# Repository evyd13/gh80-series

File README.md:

# GH80 series keyboard PCBs for Cherry boards

Please read the license before use. Each board has its own BOM and gerber files included.

These boards have been tested by numerous people, but I cannot guarantee that they work for your board.

I will not help you when you fuck up your soldering work, lol (though I might because I'm just too kind)

Oh by the way, use kicad nightly to open the source files.

## GH80-3000 vs GH80-3003
The 3000 is made by someone else, and the 3003 is mine. See it as my take on the same idea.

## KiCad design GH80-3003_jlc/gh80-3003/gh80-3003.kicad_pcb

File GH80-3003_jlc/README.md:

# GH80-3003 jlc

PCB designed by evyd13, edited to be assembled at jlcpcb by ebastler

Gerber, BOM and CPL file for jlcpcb assembly are included. They have been tested and confirmed working, but I can not guarantee that jlcpcb will not make any breaking changes. jlcpcb stocks might change, parts could go EOL. Compare MCU/diode/SRV05 rotation before ordering, to be sure.

If you order a small batch and sell the unneeded ones, please keep the license in mind.

## jlcpcb components (already in BOM/assembly files)

| Reference  | jlcpcb part # | Description    | Value    | Package  | Amount |
| ---------- | ------------- | -------------- | -------- | -------- | ------:|
| C1-C4      | C49678        | Capacitor      | 0.1 uF   | 0805     | 4      |
| C5         | C1779         | Capacitor      | 4.7 uF   | 0805     | 1      |
| C6         | C28323        | Capacitor      | 1 uF     | 0805     | 1      |
| C7, C8     | C1653         | Capacitor      | 22 pF    | 0603     | 2      |
| D1-D114    | C81598        | Diode          | 1N4148   | SOD-123  | 114    |
| F1         | C183290       | Fuse           | 750 mA   | 1206     | 1      |
| R1, R2     | C17561        | Resistor       | 22       | 0805     | 2      |
| R3, R4, R6 | C17513        | Resistor       | 1 k      | 0805     | 3      |
| R5, R6     | C17414        | Resistor       | 10 k     | 0805     | 2      |
| U1         | C44854        | MCU            | 32U4     | QFP-44   | 1      |
| U2         | C85364        | ESD Protection | SRV-05   | SOT-23-6 | 1      |
| Y1         | C13738        | Crystal        | 16 MHz   | 3225-4   | 1      |

## Other parts
| Reference  | LCSC part #   | Description   | Value    | Package  | Amount  |
| ---------- | ------------- | ------------- | -------- | -------- | -------:|
| K1-K114    |               | Keyswitch     |          | MX-like  | depends |
| L1-L3      |               | LED           |          | 3 mm THT | 3       |
| J2-J4      | C105424       | Connector     | mini USB | SMD      | 3       |
| SW1        | C92584        | Pushbutton    |          | SMD      | 1       |

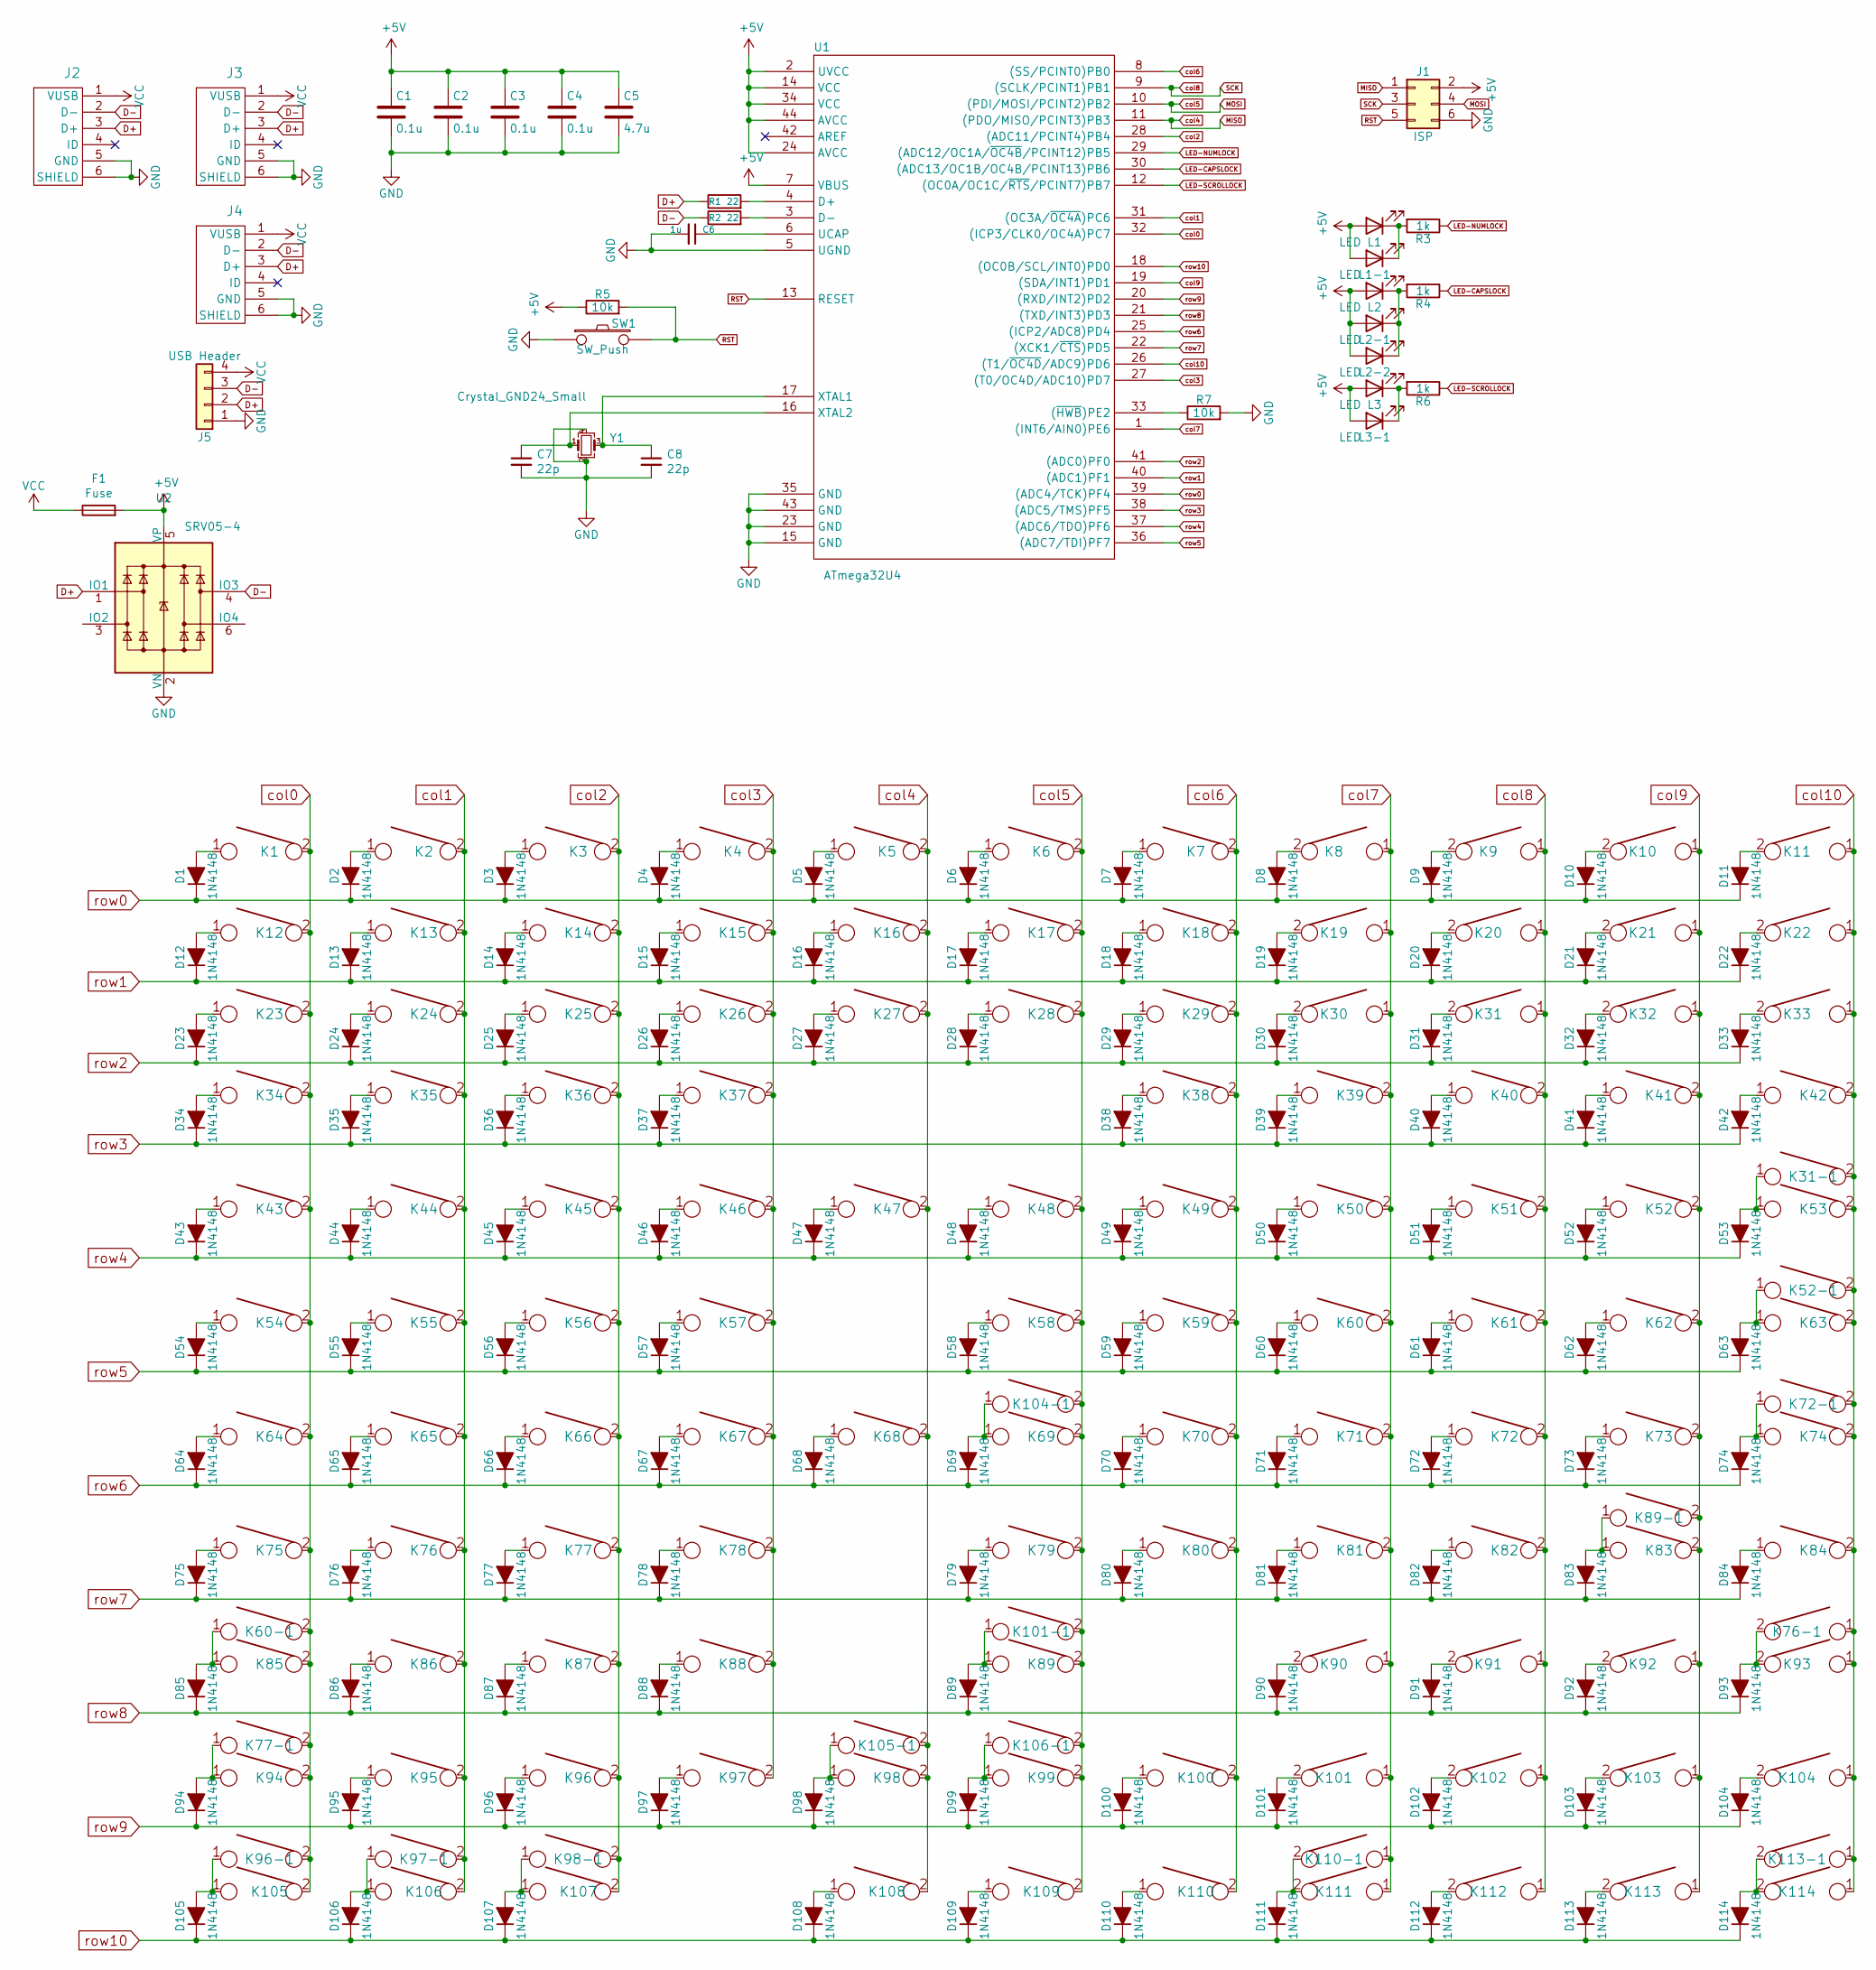
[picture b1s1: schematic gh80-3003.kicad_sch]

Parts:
C1, C2, C3, C4: 0.1u; C_0805_2012Metric; LCSC C49678
C5: 4.7u; C_0805_2012Metric; LCSC C1779
C6: 1u; C_0805_2012Metric; LCSC C28323
C7, C8: 22p; C_0603_1608Metric; LCSC C1653
D1, D2, D3, D4, D5, D6, D7, D8, D9, D10, D11, D12, D13, D14, D15, D16, D17, D18, D19, D20, D21, D22, D23, D24, D25, D26, D27, D28, D29, D30, D31, D32, D33, D34, D35, D36, D37, D38, D39, D40, D41, D42, D43, D44, D45, D46, D47, D48, D49, D50, D51, D52, D53, D54, D55, D56, D57, D58, D59, D60, D61, D62, D63, D64, D65, D66, D67, D68, D69, D70, D71, D72, D73, D74, D75, D76, D77, D78, D79, D80, D81, D82, D83, D84, D85, D86, D87, D88, D89, D90, D91, D92, D93, D94, D95, D96, D97, D98, D99, D100, D101, D102, D103, D104, D105, D106, D107, D108, D109, D110, D111, D112, D113, D114: 1N4148; D_SOD-123; LCSC C81598
F1: Fuse; Fuse_1206_3216Metric; LCSC C183290
J1: ISP; isp_standard
J2, J3, J4: USB_mini_micro_B; USB_Mini_SMD
J5: USB Header; USB_breakout
K1, K2, K3, K4, K5, K6, K7, K8, K9, K10, K11, K12, K13, K14, K15, K16, K17, K18, K19, K20, K21, K22, K24, K25, K26, K27, K28, K29, K30, K31, K31-1, K32, K33, K34, K35, K36, K37, K38, K39, K40, K41, K42, K43, K44, K45, K46, K47, K48, K49, K50, K51, K52, K52-1, K54, K55, K56, K57, K58, K59, K60, K61, K62, K64, K65, K66, K67, K70, K71, K72, K73, K75, K76, K76-1, K77, K78, K79, K80, K81, K82, K84, K86, K87, K88, K90, K91, K92, K95, K96, K97, K98, K100, K101, K102, K103, K104, K106, K108, K109, K110, K110-1, K112, K113, K113-1: KEYSW; CHERRY_PLATE_100H
K23, K63, K69, K99, K105, K107: KEYSW; CHERRY_PLATE_150H
K53, K111: KEYSW; CHERRY_PCB_200H
K60-1, K68, K77-1, K96-1, K97-1, K98-1, K104-1, K105-1, K106-1: KEYSW; CHERRY_PLATE_125H
K72-1: KEYSW; CHERRY_PCB_200H_V
K74, K94: KEYSW; CHERRY_PCB_225H
K83: KEYSW; CHERRY_PCB_275H
K85, K89-1: KEYSW; CHERRY_PLATE_175H
K89: KEYSW; CHERRY_PCB_700H
K93, K114: KEYSW; CHERRY_PCB_200H_V_F
K101-1: KEYSW; CHERRY_PCB_625H
L1, L2, L3: LED; LED_D3.0mm
L1-1, L2-1, L2-2, L3-1: LED; CHERRY_MX_LED
R1, R2: 22; R_0805_2012Metric; LCSC C17561
R3, R4, R6: 1k; R_0805_2012Metric; LCSC C17513
R5, R7: 10k; R_0805_2012Metric; LCSC C17414
SW1: SW_Push; SW_SPST_TL3342
U1: ATmega32U4; TQFP-44_10x10mm_P0.8mm; LCSC C44854
U2: SRV05-4; SOT-23-6; LCSC C85364
Y1: Crystal_GND24_Small; Crystal_SMD_3225-4Pin_3.2x2.5mm; LCSC C13738

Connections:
+5V: C1.1, C2.1, C3.1, C4.1, C5.1, F1.2, J1.2, L1.2 (A), L1-1.2 (A), L2.2 (A), L2-1.2 (A), L2-2.2 (A), L3.2 (A), L3-1.2 (A), R5.1, U1.2 (UVCC), U1.7 (VBUS), U1.14 (VCC), U1.24 (AVCC), U1.34 (VCC), U1.44 (AVCC), U2.5 (VP)
D+: J2.3 (D+), J3.3 (D+), J4.3 (D+), J5.2, R1.1, U2.1 (IO1)
D-: J2.2 (D-), J3.2 (D-), J4.2 (D-), J5.3, R2.1, U2.4 (IO3)
GND: C1.2, C2.2, C3.2, C4.2, C5.2, C6.2, C7.2, C8.2, J1.6, J2.5 (GND), J2.6 (SHIELD), J3.5 (GND), J3.6 (SHIELD), J4.5 (GND), J4.6 (SHIELD), J5.1, R7.2, SW1.1, U1.5 (UGND), U1.15 (GND), U1.23 (GND), U1.35 (GND), U1.43 (GND), U2.2 (VN), Y1.2, Y1.4
LED-CAPSLOCK: R4.1, U1.30 ((ADC13/OC1B/OC4B/PCINT13)PB6)
LED-NUMLOCK: R3.1, U1.29 ((ADC12/OC1A/~OC4B~/PCINT12)PB5)
LED-SCROLLOCK: R6.1, U1.12 ((OC0A/OC1C/~RTS~/PCINT7)PB7)
MISO: J1.1, K5.2, K16.2, K27.2, K47.2, K68.2, K98.2, K105-1.2, K108.2, U1.11 ((PDO/MISO/PCINT3)PB3)
MOSI: J1.4, K6.2, K17.2, K28.2, K48.2, K58.2, K69.2, K79.2, K89.2, K99.2, K101-1.2, K104-1.2, K106-1.2, K109.2, U1.10 ((PDI/MOSI/PCINT2)PB2)
unnamed: C6.1, U1.6 (UCAP)
unnamed: C7.1, U1.16 (XTAL2), Y1.1
unnamed: C8.1, U1.17 (XTAL1), Y1.3
unnamed: D1.2 (A), K1.1
unnamed: D2.2 (A), K2.1
unnamed: D3.2 (A), K3.1
unnamed: D4.2 (A), K4.1
unnamed: D5.2 (A), K5.1
unnamed: D6.2 (A), K6.1
unnamed: D7.2 (A), K7.1
unnamed: D8.2 (A), K8.2
unnamed: D9.2 (A), K9.2
unnamed: D10.2 (A), K10.2
unnamed: D11.2 (A), K11.2
unnamed: D12.2 (A), K12.1
unnamed: D13.2 (A), K13.1
unnamed: D14.2 (A), K14.1
unnamed: D15.2 (A), K15.1
unnamed: D16.2 (A), K16.1
unnamed: D17.2 (A), K17.1
unnamed: D18.2 (A), K18.1
unnamed: D19.2 (A), K19.2
unnamed: D20.2 (A), K20.2
unnamed: D21.2 (A), K21.2
unnamed: D22.2 (A), K22.2
unnamed: D23.2 (A), K23.1
unnamed: D24.2 (A), K24.1
unnamed: D25.2 (A), K25.1
unnamed: D26.2 (A), K26.1
unnamed: D27.2 (A), K27.1
unnamed: D28.2 (A), K28.1
unnamed: D29.2 (A), K29.1
unnamed: D30.2 (A), K30.2
unnamed: D31.2 (A), K31.2
unnamed: D32.2 (A), K32.2
unnamed: D33.2 (A), K33.2
unnamed: D34.2 (A), K34.1
unnamed: D35.2 (A), K35.1
unnamed: D36.2 (A), K36.1
unnamed: D37.2 (A), K37.1
unnamed: D38.2 (A), K38.1
unnamed: D39.2 (A), K39.1
unnamed: D40.2 (A), K40.1
unnamed: D41.2 (A), K41.1
unnamed: D42.2 (A), K42.1
unnamed: D43.2 (A), K43.1
unnamed: D44.2 (A), K44.1
unnamed: D45.2 (A), K45.1
unnamed: D46.2 (A), K46.1
unnamed: D47.2 (A), K47.1
unnamed: D48.2 (A), K48.1
unnamed: D49.2 (A), K49.1
unnamed: D50.2 (A), K50.1
unnamed: D51.2 (A), K51.1
unnamed: D52.2 (A), K52.1
unnamed: D53.2 (A), K31-1.1, K53.1
unnamed: D54.2 (A), K54.1
unnamed: D55.2 (A), K55.1
unnamed: D56.2 (A), K56.1
unnamed: D57.2 (A), K57.1
unnamed: D58.2 (A), K58.1
unnamed: D59.2 (A), K59.1
unnamed: D60.2 (A), K60.1
unnamed: D61.2 (A), K61.1
unnamed: D62.2 (A), K62.1
unnamed: D63.2 (A), K52-1.1, K63.1
unnamed: D64.2 (A), K64.1
unnamed: D65.2 (A), K65.1
unnamed: D66.2 (A), K66.1
unnamed: D67.2 (A), K67.1
unnamed: D68.2 (A), K68.1
unnamed: D69.2 (A), K69.1, K104-1.1
unnamed: D70.2 (A), K70.1
unnamed: D71.2 (A), K71.1
unnamed: D72.2 (A), K72.1
unnamed: D73.2 (A), K73.1
unnamed: D74.2 (A), K72-1.1, K74.1
unnamed: D75.2 (A), K75.1
unnamed: D76.2 (A), K76.1
unnamed: D77.2 (A), K77.1
unnamed: D78.2 (A), K78.1
unnamed: D79.2 (A), K79.1
unnamed: D80.2 (A), K80.1
unnamed: D81.2 (A), K81.1
unnamed: D82.2 (A), K82.1
unnamed: D83.2 (A), K83.1, K89-1.1
unnamed: D84.2 (A), K84.1
unnamed: D85.2 (A), K60-1.1, K85.1
unnamed: D86.2 (A), K86.1
unnamed: D87.2 (A), K87.1
unnamed: D88.2 (A), K88.1
unnamed: D89.2 (A), K89.1, K101-1.1
unnamed: D90.2 (A), K90.2
unnamed: D91.2 (A), K91.2
unnamed: D92.2 (A), K92.2
unnamed: D93.2 (A), K76-1.2, K93.2
unnamed: D94.2 (A), K77-1.1, K94.1
unnamed: D95.2 (A), K95.1
unnamed: D96.2 (A), K96.1
unnamed: D97.2 (A), K97.1
unnamed: D98.2 (A), K98.1, K105-1.1
unnamed: D99.2 (A), K99.1, K106-1.1
unnamed: D100.2 (A), K100.1
unnamed: D101.2 (A), K101.2
unnamed: D102.2 (A), K102.2
unnamed: D103.2 (A), K103.2
unnamed: D104.2 (A), K104.2
unnamed: D105.2 (A), K96-1.1, K105.1
unnamed: D106.2 (A), K97-1.1, K106.1
unnamed: D107.2 (A), K98-1.1, K107.1
unnamed: D108.2 (A), K108.1
unnamed: D109.2 (A), K109.1
unnamed: D110.2 (A), K110.1
unnamed: D111.2 (A), K110-1.2, K111.2
unnamed: D112.2 (A), K112.2
unnamed: D113.2 (A), K113.2
unnamed: D114.2 (A), K113-1.2, K114.2
unnamed: L1.1 (K), L1-1.1 (K), R3.2
unnamed: L2.1 (K), L2-1.1 (K), L2-2.1 (K), R4.2
unnamed: L3.1 (K), L3-1.1 (K), R6.2
unnamed: R1.2, U1.4 (D+)
unnamed: R2.2, U1.3 (D-)
unnamed: R7.1, U1.33 ((~HWB~)PE2)
RST: J1.5, R5.2, SW1.2, U1.13 (RESET)
SCK: J1.3, K9.1, K20.1, K31.1, K40.2, K51.2, K61.2, K72.2, K82.2, K91.1, K102.1, K112.1, U1.9 ((SCLK/PCINT1)PB1)
VCC: F1.1, J2.1 (VUSB), J3.1 (VUSB), J4.1 (VUSB), J5.4
col0: K1.2, K12.2, K23.2, K34.2, K43.2, K54.2, K60-1.2, K64.2, K75.2, K77-1.2, K85.2, K94.2, K96-1.2, K105.2, U1.32 ((ICP3/CLK0/OC4A)PC7)
col1: K2.2, K13.2, K24.2, K35.2, K44.2, K55.2, K65.2, K76.2, K86.2, K95.2, K97-1.2, K106.2, U1.31 ((OC3A/~OC4A~)PC6)
col2: K3.2, K14.2, K25.2, K36.2, K45.2, K56.2, K66.2, K77.2, K87.2, K96.2, K98-1.2, K107.2, U1.28 ((ADC11/PCINT4)PB4)
col3: K4.2, K15.2, K26.2, K37.2, K46.2, K57.2, K67.2, K78.2, K88.2, K97.2, U1.27 ((T0/OC4D/ADC10)PD7)
col6: K7.2, K18.2, K29.2, K38.2, K49.2, K59.2, K70.2, K80.2, K100.2, K110.2, U1.8 ((SS/PCINT0)PB0)
col7: K8.1, K19.1, K30.1, K39.2, K50.2, K60.2, K71.2, K81.2, K90.1, K101.1, K110-1.1, K111.1, U1.1 ((INT6/AIN0)PE6)
col9: K10.1, K21.1, K32.1, K41.2, K52.2, K62.2, K73.2, K83.2, K89-1.2, K92.1, K103.1, K113.1, U1.19 ((SDA/INT1)PD1)
col10: K11.1, K22.1, K31-1.2, K33.1, K42.2, K52-1.2, K53.2, K63.2, K72-1.2, K74.2, K76-1.1, K84.2, K93.1, K104.1, K113-1.1, K114.1, U1.26 ((T1/~OC4D~/ADC9)PD6)
row0: D1.1 (K), D2.1 (K), D3.1 (K), D4.1 (K), D5.1 (K), D6.1 (K), D7.1 (K), D8.1 (K), D9.1 (K), D10.1 (K), D11.1 (K), U1.39 ((ADC4/TCK)PF4)
row1: D12.1 (K), D13.1 (K), D14.1 (K), D15.1 (K), D16.1 (K), D17.1 (K), D18.1 (K), D19.1 (K), D20.1 (K), D21.1 (K), D22.1 (K), U1.40 ((ADC1)PF1)
row2: D23.1 (K), D24.1 (K), D25.1 (K), D26.1 (K), D27.1 (K), D28.1 (K), D29.1 (K), D30.1 (K), D31.1 (K), D32.1 (K), D33.1 (K), U1.41 ((ADC0)PF0)
row3: D34.1 (K), D35.1 (K), D36.1 (K), D37.1 (K), D38.1 (K), D39.1 (K), D40.1 (K), D41.1 (K), D42.1 (K), U1.38 ((ADC5/TMS)PF5)
row4: D43.1 (K), D44.1 (K), D45.1 (K), D46.1 (K), D47.1 (K), D48.1 (K), D49.1 (K), D50.1 (K), D51.1 (K), D52.1 (K), D53.1 (K), U1.37 ((ADC6/TDO)PF6)
row5: D54.1 (K), D55.1 (K), D56.1 (K), D57.1 (K), D58.1 (K), D59.1 (K), D60.1 (K), D61.1 (K), D62.1 (K), D63.1 (K), U1.36 ((ADC7/TDI)PF7)
row6: D64.1 (K), D65.1 (K), D66.1 (K), D67.1 (K), D68.1 (K), D69.1 (K), D70.1 (K), D71.1 (K), D72.1 (K), D73.1 (K), D74.1 (K), U1.25 ((ICP2/ADC8)PD4)
row7: D75.1 (K), D76.1 (K), D77.1 (K), D78.1 (K), D79.1 (K), D80.1 (K), D81.1 (K), D82.1 (K), D83.1 (K), D84.1 (K), U1.22 ((XCK1/~CTS~)PD5)
row8: D85.1 (K), D86.1 (K), D87.1 (K), D88.1 (K), D89.1 (K), D90.1 (K), D91.1 (K), D92.1 (K), D93.1 (K), U1.21 ((TXD/INT3)PD3)
row9: D94.1 (K), D95.1 (K), D96.1 (K), D97.1 (K), D98.1 (K), D99.1 (K), D100.1 (K), D101.1 (K), D102.1 (K), D103.1 (K), D104.1 (K), U1.20 ((RXD/INT2)PD2)
row10: D105.1 (K), D106.1 (K), D107.1 (K), D108.1 (K), D109.1 (K), D110.1 (K), D111.1 (K), D112.1 (K), D113.1 (K), D114.1 (K), U1.18 ((OC0B/SCL/INT0)PD0)

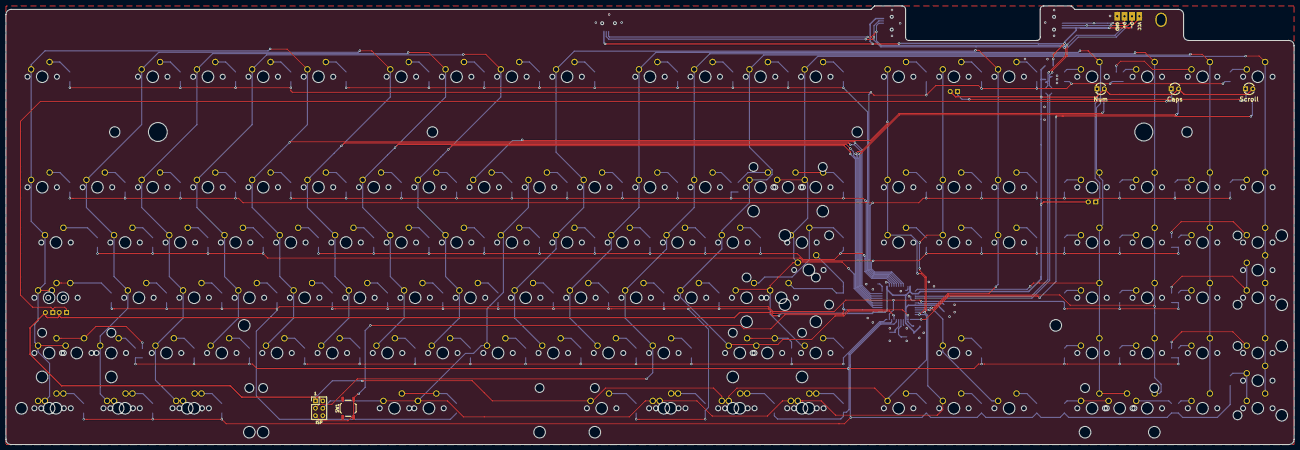
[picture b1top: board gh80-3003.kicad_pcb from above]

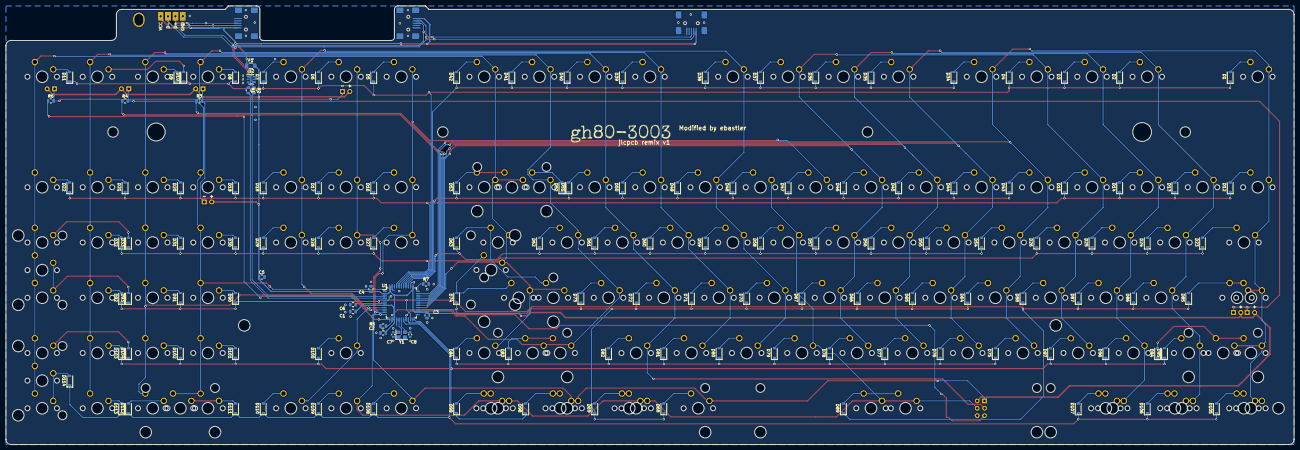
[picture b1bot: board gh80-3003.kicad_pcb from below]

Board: 2 copper layers, 444.1 x 151.2 mm, 276 parts (136 on the bottom side), 154 nets.

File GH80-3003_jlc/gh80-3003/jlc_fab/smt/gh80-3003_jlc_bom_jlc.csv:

"Comment","Designator","Footprint","LCSC Part #"
"0.1u","C1,C2,C3,C4","C_0805_2012Metric","C49678"
"4.7u","C5","C_0805_2012Metric","C1779"
"1u","C6","C_0805_2012Metric","C28323"
"22p","C7,C8","C_0603_1608Metric","C1653"
"1N4148","D1,D2,D3,D4,D5,D6,D7,D8,D9,D10,D11,D12,D13,D14,D15,D16,D17,D18,D19,D20,D21,D22,D23,D24,D25,D26,D27,D28,D29,D30,D31,D32,D33,D34,D35,D36,D37,D38,D39,D40,D41,D42,D43,D44,D45,D46,D47,D48,D49,D50,D51,D52,D53,D54,D55,D56,D57,D58,D59,D60,D61,D62,D63,D64,D65,D66,D67,D68,D69,D70,D71,D72,D73,D74,D75,D76,D77,D78,D79,D80,D81,D82,D83,D84,D85,D86,D87,D88,D89,D90,D91,D92,D93,D94,D95,D96,D97,D98,D99,D100,D101,D102,D103,D104,D105,D106,D107,D108,D109,D110,D111,D112,D113,D114","D_SOD-123","C81598"
"Fuse","F1","Fuse_1206_3216Metric","C183290"
"22","R1,R2","R_0805_2012Metric","C17561"
"1k","R3,R4,R6","R_0805_2012Metric","C17513"
"10k","R5,R7","R_0805_2012Metric","C17414"
"ATmega32U4","U1","TQFP-44_10x10mm_P0.8mm","C44854"
"SRV05-4","U2","SOT-23-6","C85364"
"Crystal_GND24_Small","Y1","Crystal_SMD_3225-4Pin_3.2x2.5mm","C13738"

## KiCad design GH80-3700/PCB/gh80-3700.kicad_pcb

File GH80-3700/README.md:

# GH80-3700

## BOM main pcb

| LCSC part # | Description   | Value | Package  | Amount |
| ----------- | ------------- | ----- | -------- | ------:|
| C128353     | Capacitor     | 0.1uF | 0805     | 4      |
| C131056     | Capacitor     | 4.7uF | 0805     | 1      |
| C215803     | Capacitor     | 1uF   | 0805     | 1      |
| C109001     | Diode         |       | 0805     | 24     |
| C165948     | Connector     |       | SMD/THT  | 1      |
| C103904     | Resistor      | 10K   | 0805     | 2      |
| C212411     | Resistor      | 5.1K  | 0805     | 2      |
| C384174     | Resistor      | 1K    | 0805     | 5      |
| C325772     | Resistor      | 22    | 0805     | 2      |
| C44854      | MCU           | 32U4  | QFP-44   | 1      |
| C7519       | ESD chip      |       | SOT23-6  | 1      |
| C261942     | Fuse          |       | 0805     | 1      |
| C341521     | Resonator     | 16MHz | SMD      | 1      |
| C223806     | Switch        |       | THT      | 1      |

## BOM daughterboard (speaker and ps/2 port) pcb

It's a little expansion board to be able to use a speaker or PS/2 mouse, or just to fill up that hole in the case.

| LCSC part # | Description   | Value | Package  | Amount |
| ----------- | ------------- | ----- | -------- | ------:|
| C131056     | Capacitor     | 4.7uF | 0805     | 1      |
| C17673      | Resistor      | 4.7K  | 0805     | 2      |
| C261942     | Fuse          |       | 0805     | 1      |
| C136657     | JST SH 5 pin  |       | SMD      | 2      |
|  C77848     | PS2 connector |       | THT      | 1      |

You'll also need a JST SH 5 pin cable for this one. Those can be found on aliexpress or similar sites.

Use at your own risk.

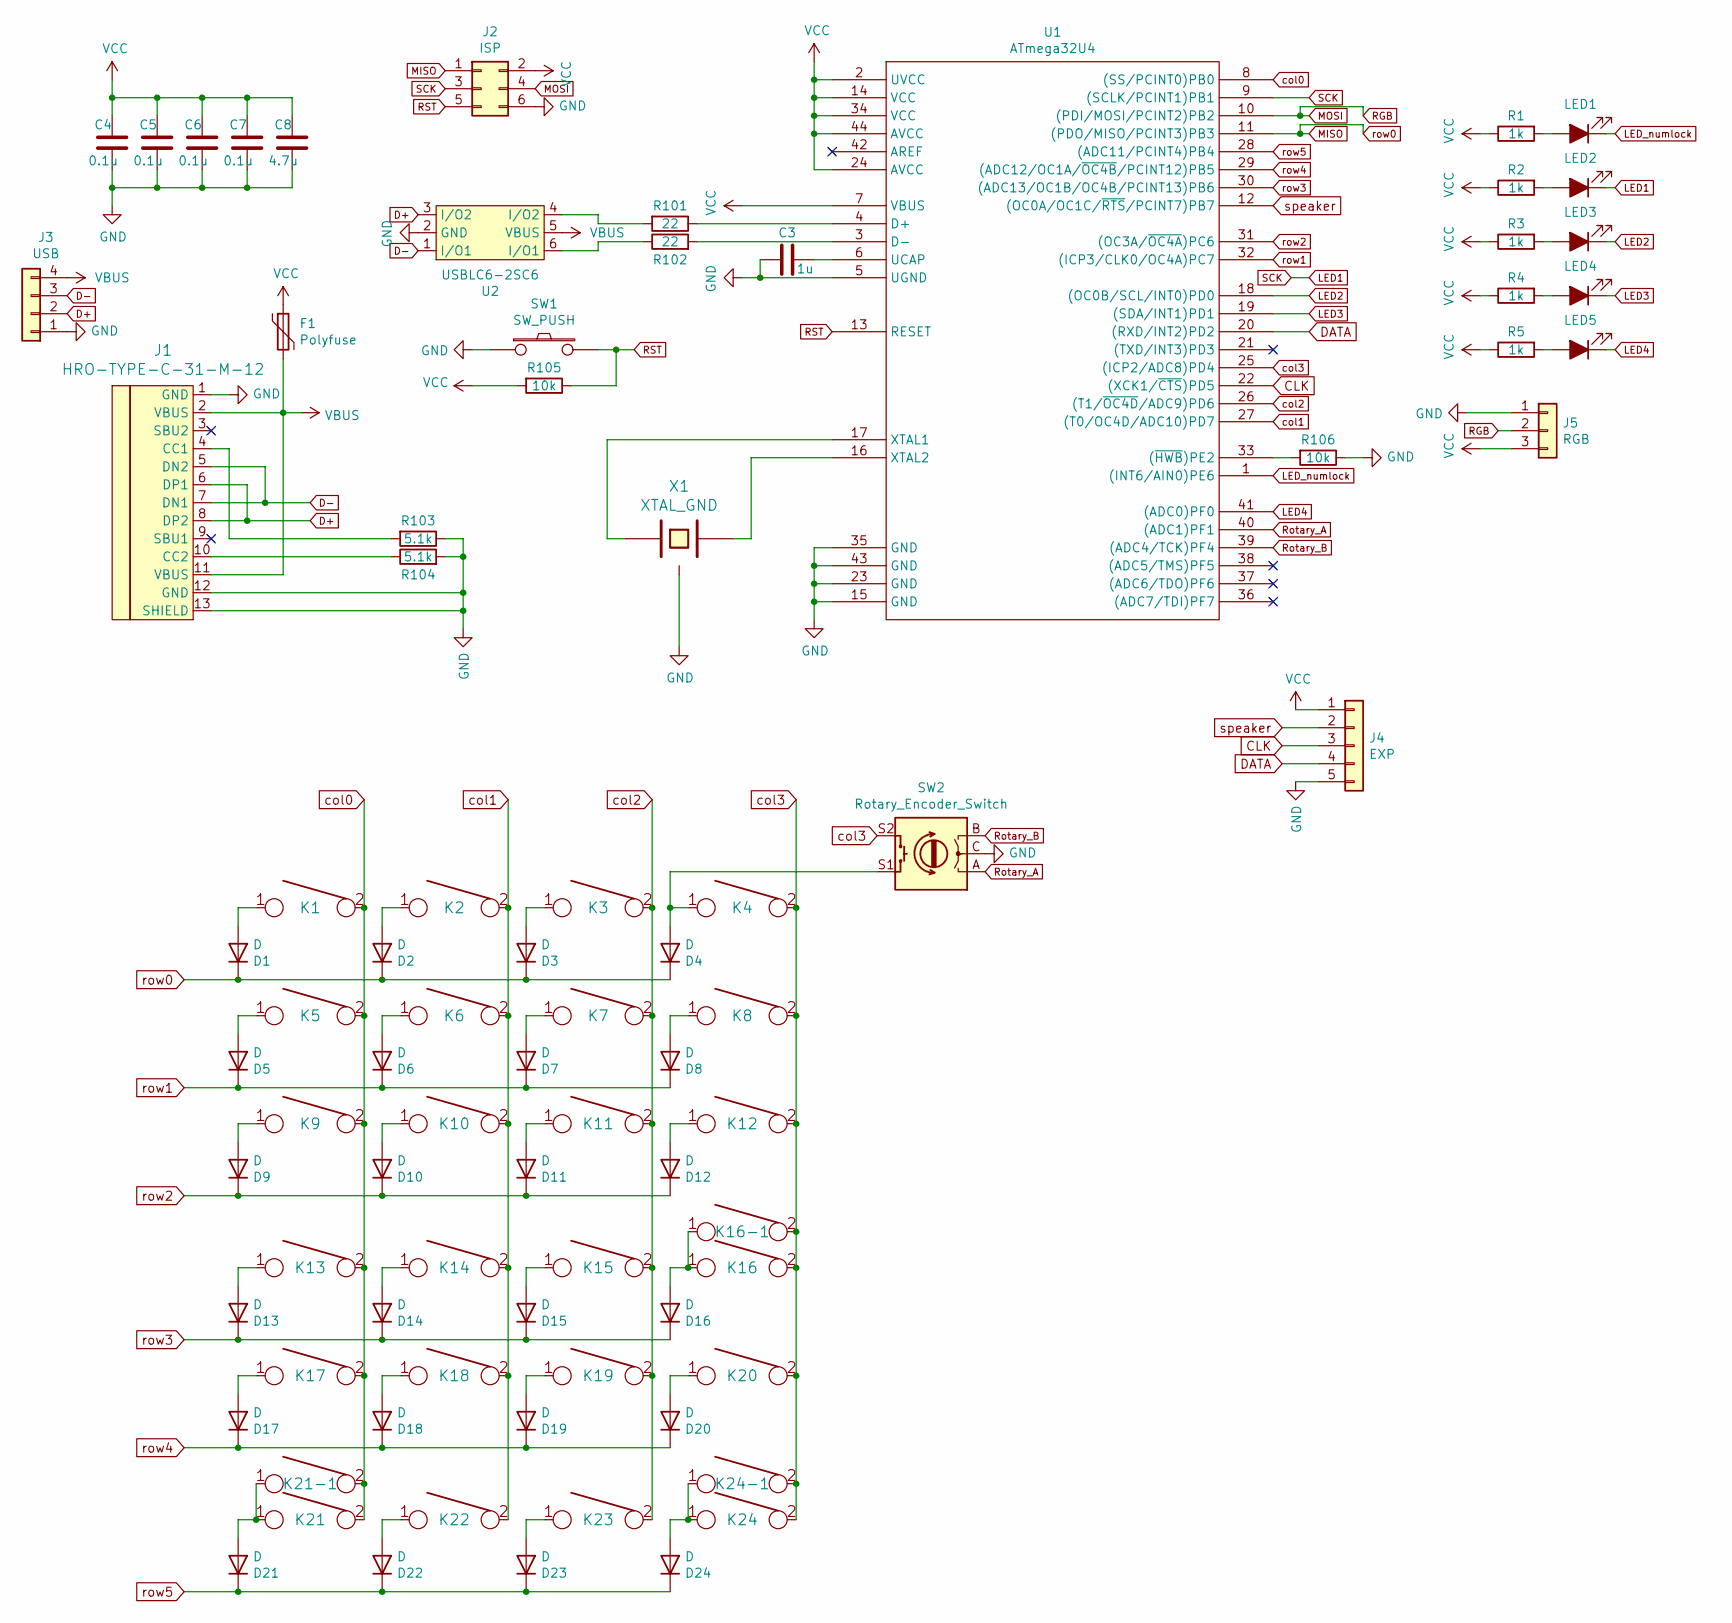
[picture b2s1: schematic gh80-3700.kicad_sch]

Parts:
C3: 1u; C_0805
C4, C5, C6, C7: 0.1u; C_0805
C8: 4.7u; C_0805
D1, D2, D3, D4, D5, D6, D7, D8, D9, D10, D11, D12, D13, D14, D15, D16, D17, D18, D19, D20, D21, D22, D23, D24: D; D_0805
F1: Polyfuse; R_0805
J1: HRO-TYPE-C-31-M-12
J2: ISP; isp_standard
J3: USB; USB_breakout
J4: EXP; JST_SH_SM05B-SRSS-TB_1x05-1MP_P1.00mm_Horizontal
J5: RGB; PinHeader_1x03_P2.54mm_Vertical
K1, K2, K3, K4, K5, K6, K7, K8, K9, K10, K11, K12, K13, K14, K15, K16, K17, K18, K19, K20, K21, K22, K23, K24: KEYSW; CHERRY_PLATE_100H
K16-1, K24-1: KEYSW; CHERRY_PCB_200H_V
K21-1: KEYSW; CHERRY_PCB_200H
LED1, LED2, LED3, LED4, LED5: LED_ALT; CHERRY_MX_LED
R1, R2, R3, R4, R5: 1k; R_0805
R101, R102: 22; R_0805
R103, R104: 5.1k; R_0805
R105, R106: 10k; R_0805
SW1: SW_PUSH; HRO_K2-1109DE-D4SW-01
SW2: Rotary_Encoder_Switch; RotaryEncoder_Alps_EC11
U1: ATmega32U4; ATMEGA32U4
U2: USBLC6-2SC6; Farnell 1295310
X1: XTAL_GND; Resonator_SMD_muRata_CSTNExxV-3Pin-p1.2

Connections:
CLK: J4.3, U1.22 ((XCK1/~CTS~)PD5)
D+: J1.6 (DP1), J1.8 (DP2), J3.2, U2.3 (I/O2)
D-: J1.5 (DN2), J1.7 (DN1), J3.3, U2.1 (I/O1)
DATA: J4.4, U1.20 ((RXD/INT2)PD2)
GND: C3.2, C4.1, C5.1, C6.1, C7.1, C8.1, J1.1 (GND), J1.12 (GND), J1.13 (SHIELD), J2.6, J3.1, J4.5, J5.1, R103.1, R104.2, R106.1, SW1.1, SW2.C, U1.5 (UGND), U1.15 (GND), U1.23 (GND), U1.35 (GND), U1.43 (GND), U2.2 (GND), X1.3
LED1: J2.3, LED2.1 (K), U1.9 ((SCLK/PCINT1)PB1)
LED2: LED3.1 (K), U1.18 ((OC0B/SCL/INT0)PD0)
LED3: LED4.1 (K), U1.19 ((SDA/INT1)PD1)
LED4: LED5.1 (K), U1.41 ((ADC0)PF0)
LED_numlock: LED1.1 (K), U1.1 ((INT6/AIN0)PE6)
MISO: D1.1 (K), D2.1 (K), D3.1 (K), D4.1 (K), J2.1, U1.11 ((PDO/MISO/PCINT3)PB3)
MOSI: J2.4, J5.2, U1.10 ((PDI/MOSI/PCINT2)PB2)
unnamed: C3.1, U1.6 (UCAP)
unnamed: D1.2 (A), K1.1
unnamed: D2.2 (A), K2.1
unnamed: D3.2 (A), K3.1
unnamed: D4.2 (A), K4.1, SW2.S1
unnamed: D5.2 (A), K5.1
unnamed: D6.2 (A), K6.1
unnamed: D7.2 (A), K7.1
unnamed: D8.2 (A), K8.1
unnamed: D9.2 (A), K9.1
unnamed: D10.2 (A), K10.1
unnamed: D11.2 (A), K11.1
unnamed: D12.2 (A), K12.1
unnamed: D13.2 (A), K13.1
unnamed: D14.2 (A), K14.1
unnamed: D15.2 (A), K15.1
unnamed: D16.2 (A), K16.1, K16-1.1
unnamed: D17.2 (A), K17.1
unnamed: D18.2 (A), K18.1
unnamed: D19.2 (A), K19.1
unnamed: D20.2 (A), K20.1
unnamed: D21.2 (A), K21.1, K21-1.1
unnamed: D22.2 (A), K22.1
unnamed: D23.2 (A), K23.1
unnamed: D24.2 (A), K24.1, K24-1.1
unnamed: J1.4 (CC1), R103.2
unnamed: J1.10 (CC2), R104.1
unnamed: LED1.2 (A), R1.2
unnamed: LED2.2 (A), R2.2
unnamed: LED3.2 (A), R3.2
unnamed: LED4.2 (A), R4.2
unnamed: LED5.2 (A), R5.2
unnamed: R101.1, U1.4 (D+)
unnamed: R101.2, U2.4 (I/O2)
unnamed: R102.1, U2.6 (I/O1)
unnamed: R102.2, U1.3 (D-)
unnamed: R106.2, U1.33 ((~HWB~)PE2)
unnamed: U1.16 (XTAL2), X1.2
unnamed: U1.17 (XTAL1), X1.1
RST: J2.5, R105.1, SW1.2, U1.13 (RESET)
Rotary_A: SW2.A, U1.40 ((ADC1)PF1)
Rotary_B: SW2.B, U1.39 ((ADC4/TCK)PF4)
VBUS: F1.2, J1.2 (VBUS), J1.11 (VBUS), J3.4, U2.5 (VBUS)
VCC: C4.2, C5.2, C6.2, C7.2, C8.2, F1.1, J2.2, J4.1, J5.3, R1.1, R2.1, R3.1, R4.1, R5.1, R105.2, U1.2 (UVCC), U1.7 (VBUS), U1.14 (VCC), U1.24 (AVCC), U1.34 (VCC), U1.44 (AVCC)
col0: K1.2, K5.2, K9.2, K13.2, K17.2, K21.2, K21-1.2, U1.8 ((SS/PCINT0)PB0)
col1: K2.2, K6.2, K10.2, K14.2, K18.2, K22.2, U1.27 ((T0/OC4D/ADC10)PD7)
col2: K3.2, K7.2, K11.2, K15.2, K19.2, K23.2, U1.26 ((T1/~OC4D~/ADC9)PD6)
col3: K4.2, K8.2, K12.2, K16.2, K16-1.2, K20.2, K24.2, K24-1.2, SW2.S2, U1.25 ((ICP2/ADC8)PD4)
row1: D5.1 (K), D6.1 (K), D7.1 (K), D8.1 (K), U1.32 ((ICP3/CLK0/OC4A)PC7)
row2: D9.1 (K), D10.1 (K), D11.1 (K), D12.1 (K), U1.31 ((OC3A/~OC4A~)PC6)
row3: D13.1 (K), D14.1 (K), D15.1 (K), D16.1 (K), U1.30 ((ADC13/OC1B/OC4B/PCINT13)PB6)
row4: D17.1 (K), D18.1 (K), D19.1 (K), D20.1 (K), U1.29 ((ADC12/OC1A/~OC4B~/PCINT12)PB5)
row5: D21.1 (K), D22.1 (K), D23.1 (K), D24.1 (K), U1.28 ((ADC11/PCINT4)PB4)
speaker: J4.2, U1.12 ((OC0A/OC1C/~RTS~/PCINT7)PB7)

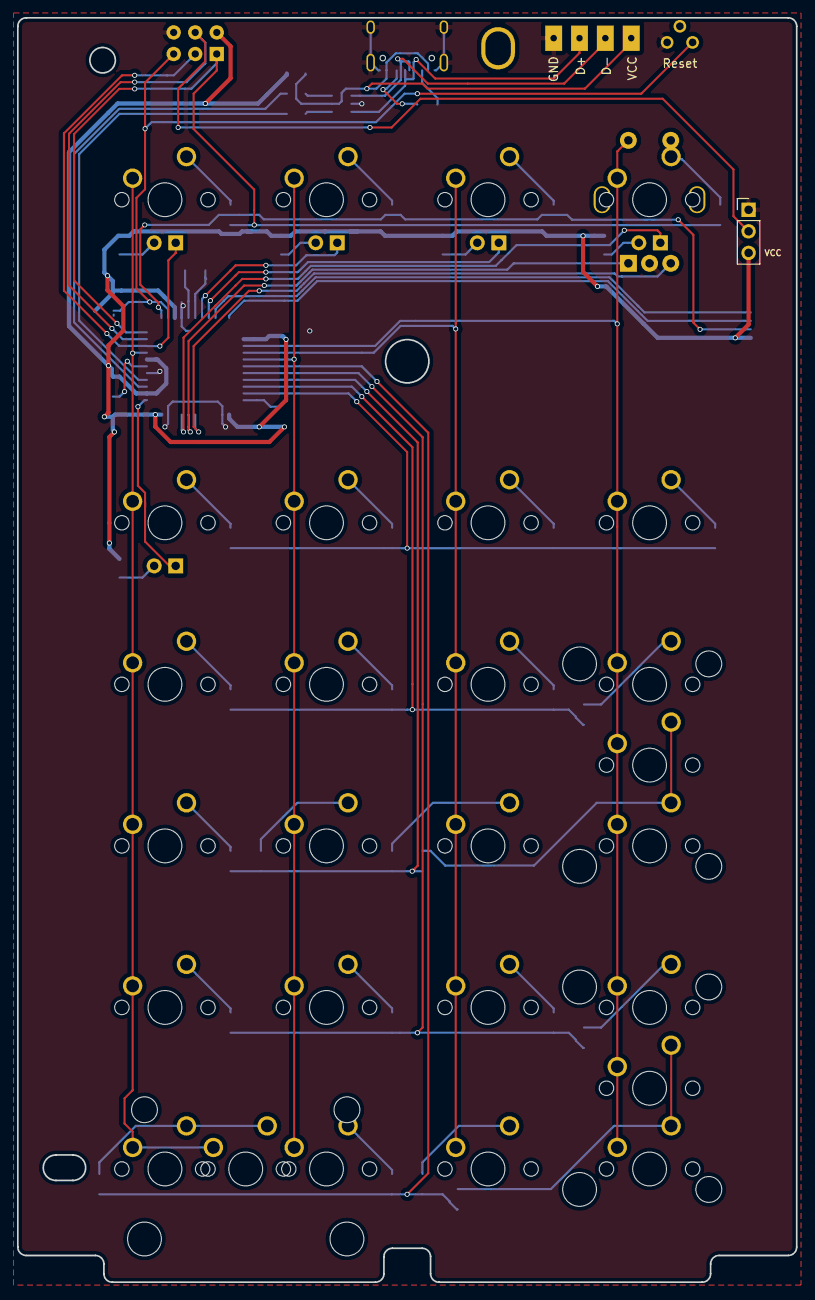
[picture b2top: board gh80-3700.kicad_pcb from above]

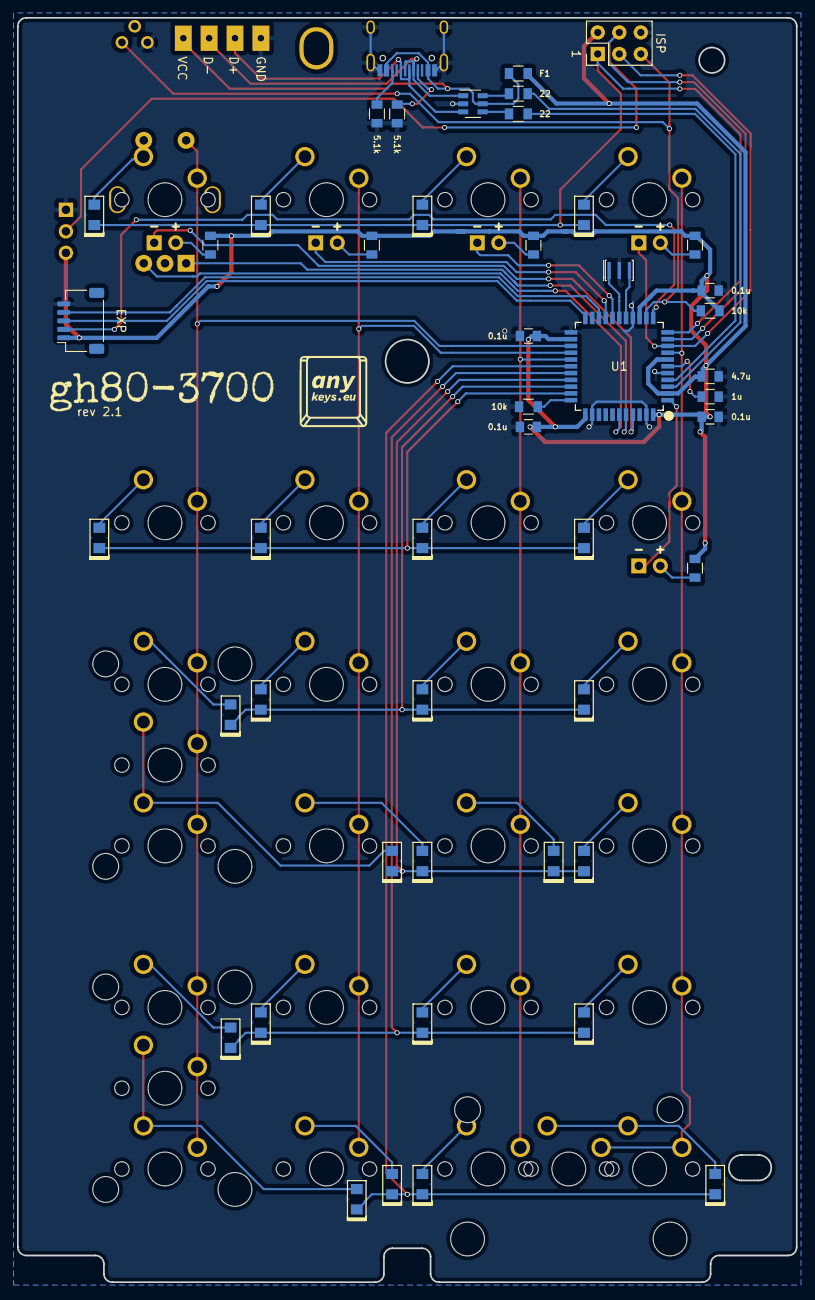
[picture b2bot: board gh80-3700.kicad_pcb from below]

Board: 2 copper layers, 91.8 x 149.1 mm, 84 parts (48 on the bottom side), 66 nets.

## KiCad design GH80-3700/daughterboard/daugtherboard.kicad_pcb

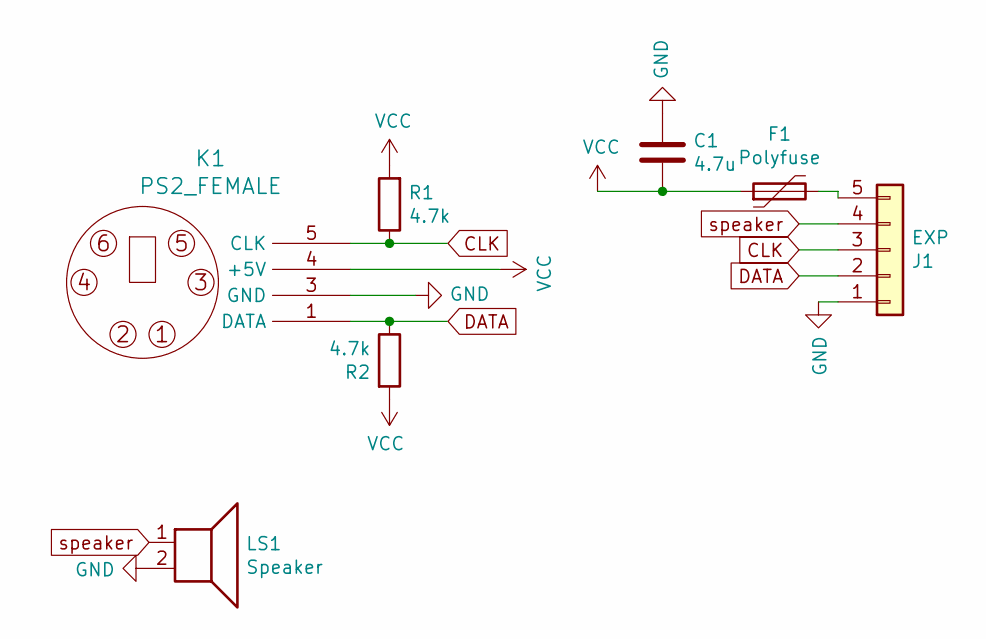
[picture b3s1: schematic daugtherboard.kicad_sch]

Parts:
C1: 4.7u; C_0805
F1: Polyfuse; R_0805
J1: EXP; JST_SH_SM05B-SRSS-TB_1x05-1MP_P1.00mm_Horizontal
K1: PS2_FEMALE; ps2_connector
LS1: Speaker; speaker_AST1109MLTRQ
R1, R2: 4.7k; R_0805

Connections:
CLK: J1.3, K1.5 (CLK), R1.1
DATA: J1.2, K1.1 (DATA), R2.1
GND: C1.2, J1.1, K1.3 (GND), LS1.2
unnamed: F1.2, J1.5
VCC: C1.1, F1.1, K1.4 (+5V), R1.2, R2.2
speaker: J1.4, LS1.1

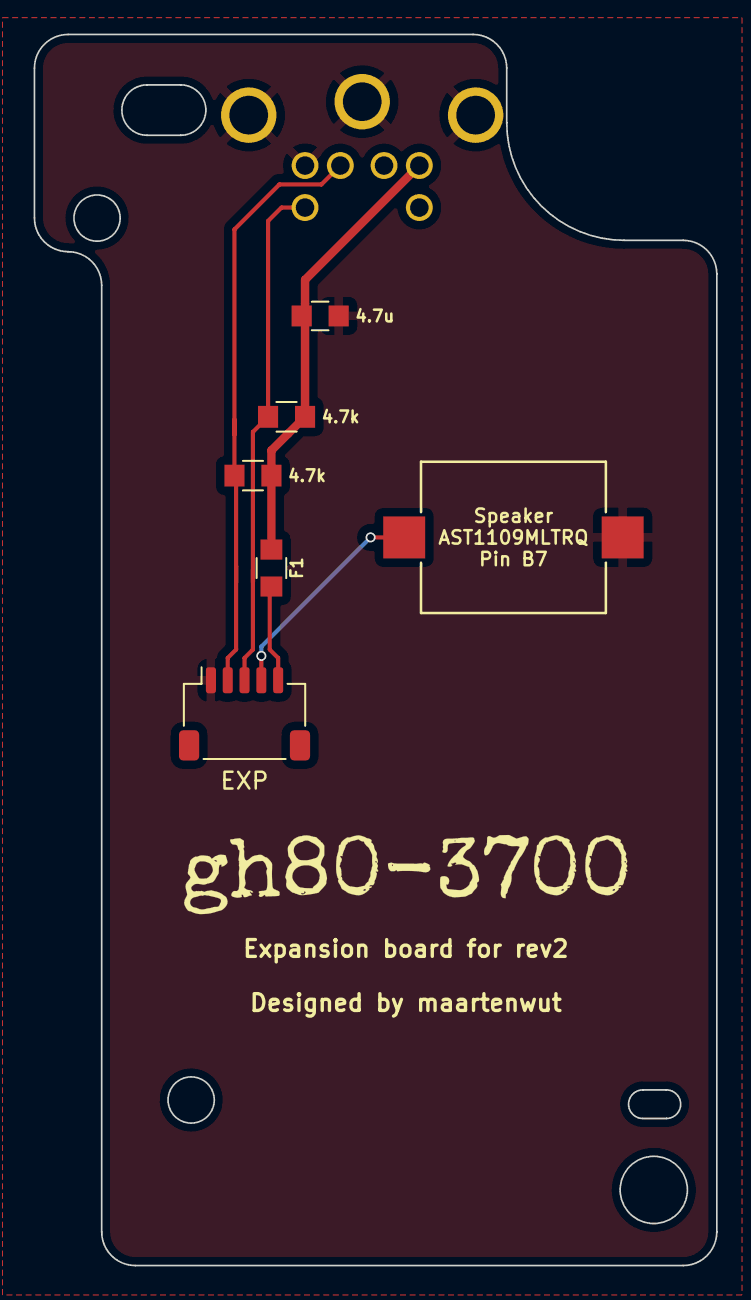
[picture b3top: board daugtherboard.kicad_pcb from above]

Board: 2 copper layers, 40.6 x 73.2 mm, 7 parts (0 on the bottom side), 6 nets.

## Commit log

2020-07-01 Upload files
2020-08-30 Update LICENSE
2020-09-26 Add website logo/remove maartenwut
2020-10-01 Add 3d printable case
2020-10-03 add gh80-3003 jlcpcb fab remix
2020-10-03 fixed readme heading
2021-04-03 Upload GH80-3003 plate
